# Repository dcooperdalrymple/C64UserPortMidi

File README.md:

# Commodore 64 User Port Midi Device
> Simple Midi Input & Output via the Commodore 64 User Port Interface<br />
> Created by D Cooper Dalrymple 2021 - [dcdalrymple.com](https://dcdalrymple.com/)<br />
> Licensed under GNU GPL V3.0<br />

I found myself in possession of a Commodore SX-64 and a desire to make music with it. After quickly finding [Cynthcart](https://www.qotile.net/cynthcart.html), I wasn't too happy about the idea of plugging both the Cynthcart cartridge and a separate Datel midi cartridge into in a [Mini X-Pander+](http://www.arkanixlabs.com/minixpander/) all sticking out of the hood of my SX-64. I had assumed that the User Port would have been a great interface for transmitting the necessary midi input data to whatever SID program you're jamming with. That's where this project comes in.

## Functionality
The concept is fairly simple: the stream of data from the midi input will be piped into a buffer by the microcontroller. After representing the value of each byte on the data bus of the user port (PB0-7), it will then trigger the user port's flag interrupt (FLAG2) to indicate new data is available. The compatible Commodore software that has an interrupt registered for the user port's flag pin then adds that 8-bit data register to a data buffer. The midi information would then need to be processed by the main loop of the software. Easy peasy!

I am aware that there are serial lines available on the user port that have been used for RS-232 communication and such, but I wanted to use the least amount of resources when transferring data from the bus to the Commodore software. A simple `lda $DD01` is all that is necessary to get the full byte during a flag interrupt.

The 8 bits of the user port are bi-directionally connected to the microcontroller, and a data transfer back to the microcontroller can be flagged using the dedicated GPIO pin, PC2. This functionality can be used to send midi data back out through the Midi Out port and perform additional functionality that has yet to be developed (channel filters, etc).

## Components
The microcontroller chosen for this project is the ATtiny2313. Using this micro reduces the total BOM by not requiring an external crystal oscillator, operating at 5V, including a hardware UART controller, and having just the right amount of GPIO.

Overall, the BOM is fairly minimal and using only through-hole components for easy assembly. To quickly get started making your own, I've assembled a [Digikey shared cart](https://www.digikey.com/short/7djhm4fz) with the exact hardware requirements and all of the necessary gerber files to order your own PCBs from a distributor such as PCBway.

## Development Status
I've just completed revision A of the hardware design which migrated from the ATtiny13 to ATtiny2313 and removed the need for a shift register. I've also added the components required MIDI output since the new microcontroller should be able to handle UART transmission with ease.

The firmware hasn't yet been updated for this new board design, but the functionality should mostly remain the same within the C64 software. I'll provide examples of bidirectional data transfer showcasing the output functionality of the new board once any bugs have been worked out.

I advise from producing your own units until the hardware and software have been fully developed.

## Software
A testing cartridge for the C64 is in development and mostly complete. This easily fits on a small 4kb/8kb lo-rom cart and could be compiled for floppy if needed. It can be run in emulation, but it isn't very useful unless the debugging data is enabled.

I plan to fork the Cynthcart repo once testing is completed to include full compatibility with this device.

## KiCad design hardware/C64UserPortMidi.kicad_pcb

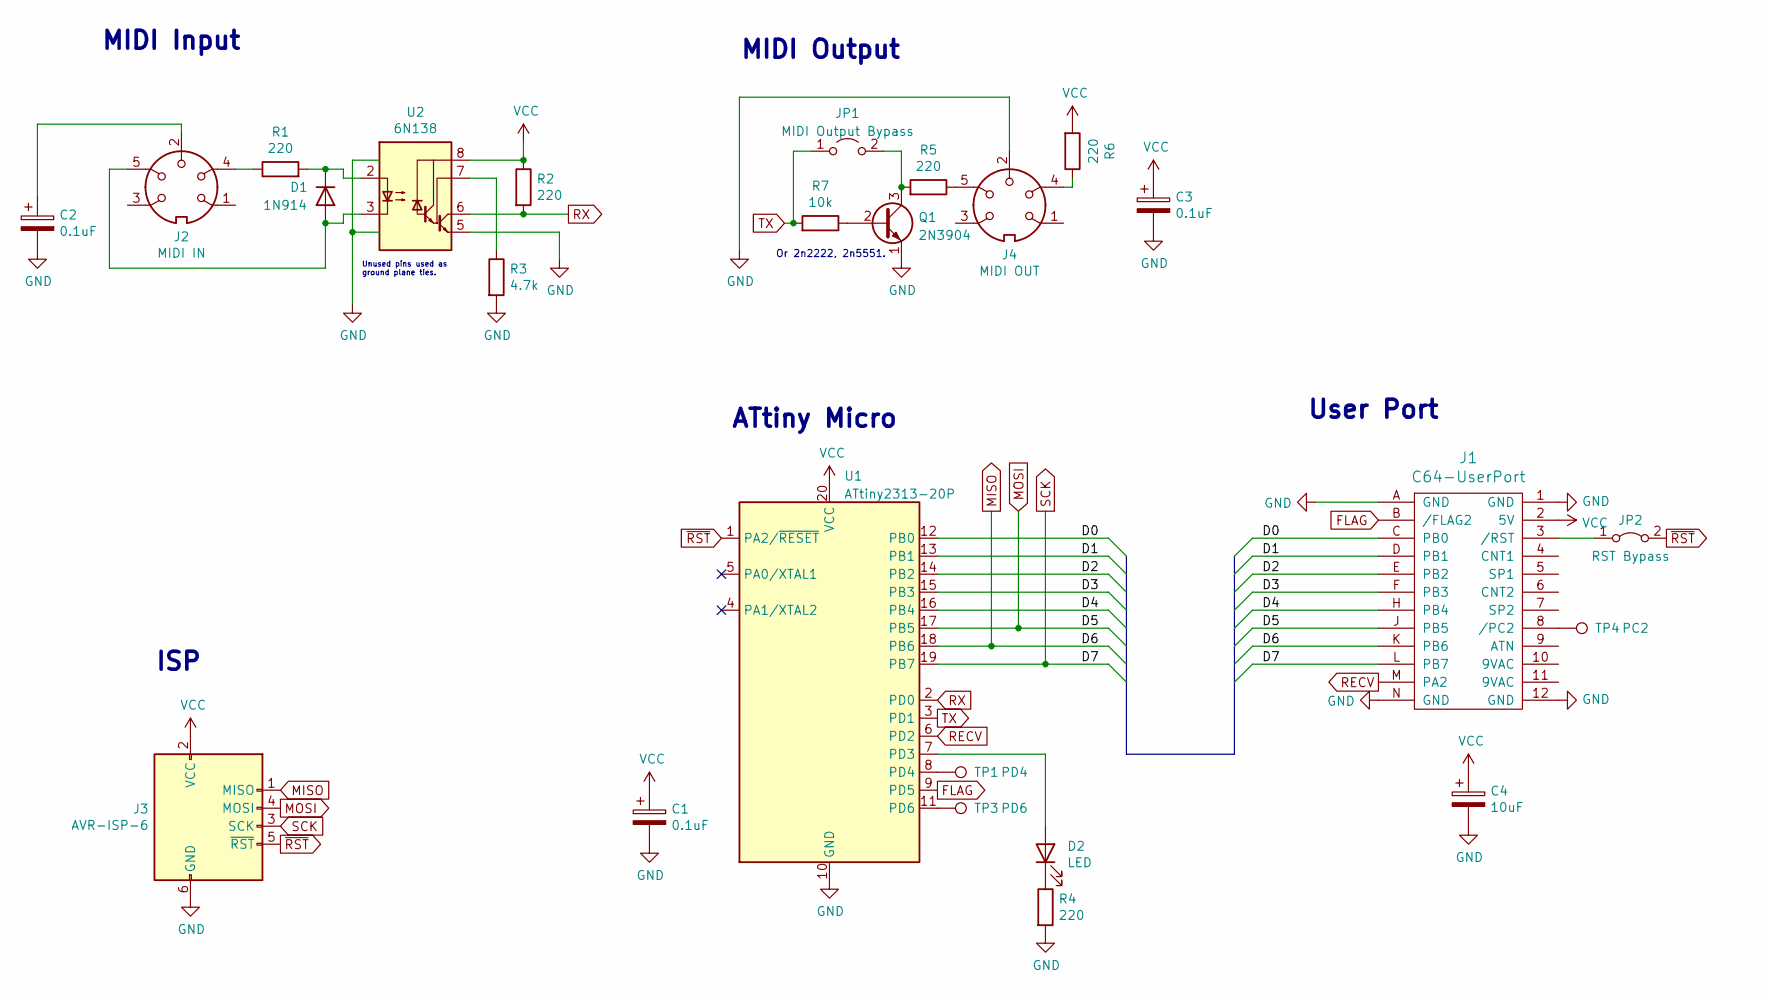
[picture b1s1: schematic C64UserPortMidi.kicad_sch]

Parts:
C1, C2, C3: 0.1uF; CP_Radial_D5.0mm_P2.00mm
C4: 10uF; CP_Radial_D5.0mm_P2.00mm
D1: 1N914; D_DO-35_SOD27_P7.62mm_Horizontal
D2: LED; LED_D3.0mm
J1: C64-UserPort; Connector_Edge_2x12_P3.96mm
J2: MIDI IN; din-5
J3: AVR-ISP-6; PinHeader_2x03_P2.54mm_Vertical
J4: MIDI OUT; din-5
JP1: MIDI Output Bypass; SolderJumper-2_P1.3mm_Open_RoundedPad1.0x1.5mm
JP2: RST Bypass; SolderJumper-2_P1.3mm_Bridged_RoundedPad1.0x1.5mm
Q1: 2N3904; TO-92_Inline
R1, R2, R4, R5, R6: 220; R_Axial_DIN0207_L6.3mm_D2.5mm_P7.62mm_Horizontal
R3: 4.7k; R_Axial_DIN0207_L6.3mm_D2.5mm_P7.62mm_Horizontal
R7: 10k; R_Axial_DIN0207_L6.3mm_D2.5mm_P7.62mm_Horizontal
TP1: PD4; TestPoint_THTPad_D1.5mm_Drill0.7mm
TP3: PD6; TestPoint_THTPad_D1.5mm_Drill0.7mm
TP4: PC2; TestPoint_THTPad_D1.5mm_Drill0.7mm
U1: ATtiny2313-20P; DIP-20_W7.62mm_Socket_LongPads
U2: 6N138; DIP-8_W7.62mm_Socket_LongPads

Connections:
/D0: J1.C (PB0), U1.12 (PB0)
/D1: J1.D (PB1), U1.13 (PB1)
/D2: J1.E (PB2), U1.14 (PB2)
/D3: J1.F (PB3), U1.15 (PB3)
/D4: J1.H (PB4), U1.16 (PB4)
FLAG: J1.B (/FLAG2), U1.9 (PD5)
GND: C1.2, C2.2, C3.2, C4.2, J1.1 (GND), J1.12 (GND), J1.A (GND), J1.N (GND), J3.6 (GND), J4.2, Q1.1 (E), R3.2, R4.2, U1.10 (GND), U2.1 (NC), U2.4 (NC), U2.5 (GND)
MISO: J1.K (PB6), J3.1 (MISO), U1.18 (PB6)
MOSI: J1.J (PB5), J3.4 (MOSI), U1.17 (PB5)
unnamed: C2.1, J2.2
unnamed: D1.1 (K), R1.2, U2.2 (C1)
unnamed: D1.2 (A), J2.5, U2.3 (C2)
unnamed: D2.1 (K), R4.1
unnamed: D2.2 (A), U1.7 (PD3)
unnamed: J1.3 (/RST), JP2.1 (A)
unnamed: J1.8 (/PC2), TP4.1
unnamed: J2.4, R1.1
unnamed: J4.4, R6.1
unnamed: J4.5, R5.1
unnamed: JP1.2 (B), Q1.3 (C), R5.2
unnamed: Q1.2 (B), R7.1
unnamed: R3.1, U2.7 (VO1)
unnamed: TP1.1, U1.8 (PD4)
unnamed: TP3.1, U1.11 (PD6)
RECV: J1.M (PA2), U1.6 (PD2)
RX: R2.2, U1.2 (PD0), U2.6 (VO2)
SCK: J1.L (PB7), J3.3 (SCK), U1.19 (PB7)
TX: JP1.1 (A), R7.2, U1.3 (PD1)
VCC: C1.1, C3.1, C4.1, J1.2 (5V), J3.2 (VCC), R2.1, R6.2, U1.20 (VCC), U2.8 (VCC)
~RST: J3.5 (~RST), JP2.2 (B), U1.1 (PA2/~RESET)

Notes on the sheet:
MIDI Input
MIDI Output
Or 2n2222, 2n5551.
User Port
ATtiny Micro
Unused pins used as ground plane ties.
ISP

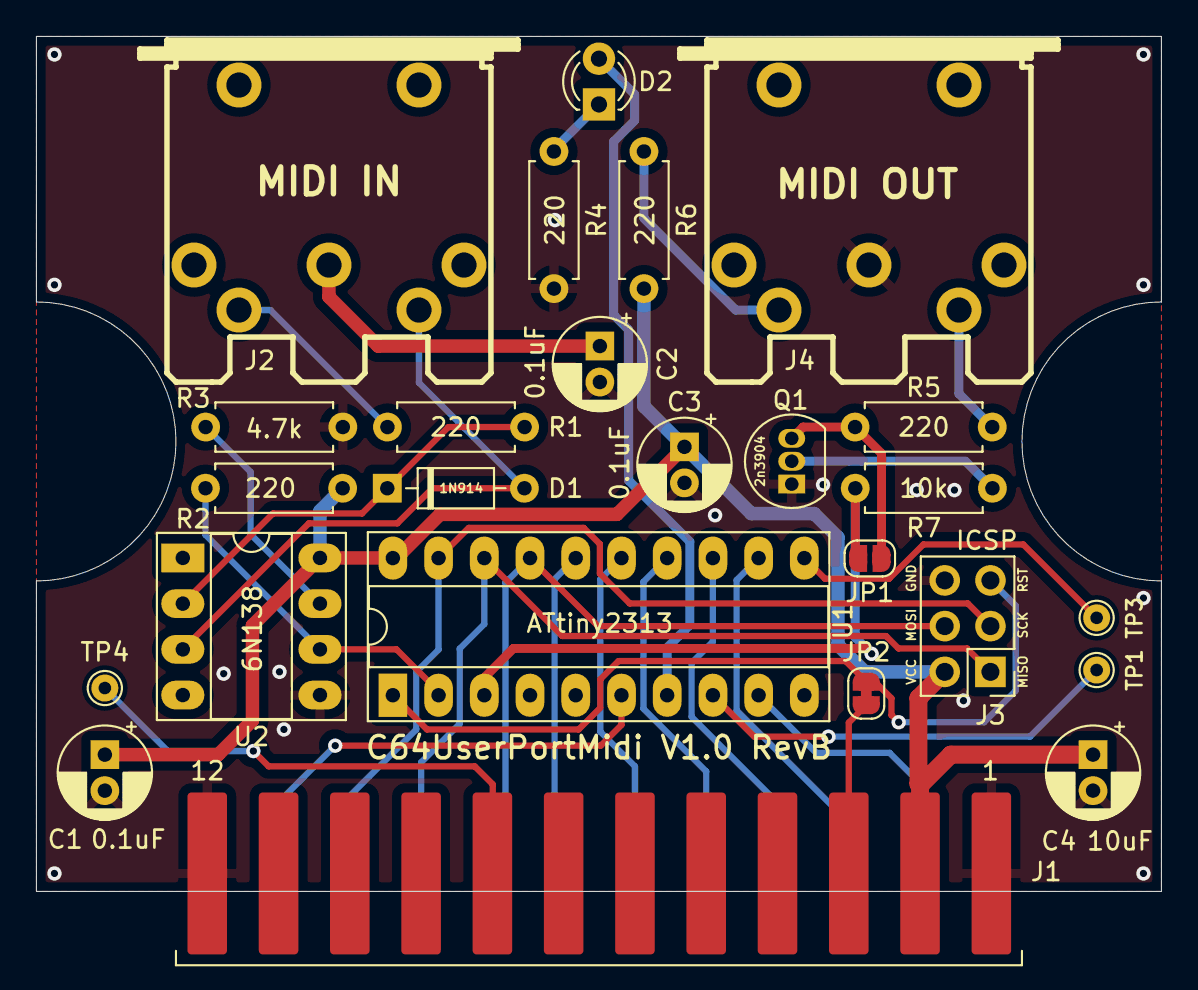
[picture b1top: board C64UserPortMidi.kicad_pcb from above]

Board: 2 copper layers, 62.5 x 47.5 mm, 25 parts (0 on the bottom side), 30 nets.

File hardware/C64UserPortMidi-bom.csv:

Reference, Value, Footprint, Datasheet
"C1","0.1uF","Capacitor_THT:CP_Radial_D5.0mm_P2.00mm",""
"C2","0.1uF","Capacitor_THT:CP_Radial_D5.0mm_P2.00mm",""
"C3","0.1uF","Capacitor_THT:CP_Radial_D5.0mm_P2.00mm",""
"C4","10uF","Capacitor_THT:CP_Radial_D5.0mm_P2.00mm",""
"D1","1N914","Diode_THT:D_DO-35_SOD27_P7.62mm_Horizontal","http://www.vishay.com/docs/85622/1n914.pdf"
"D2","LED","LED_THT:LED_D3.0mm",""
"J1","C64-UserPort","Commodore64C:Connector_Edge_2x12_P3.96mm",""
"J2","MIDI IN","Video Connectors:din-5","http://www.mouser.com/ds/2/18/40_c091_abd_e-75918.pdf"
"J3","AVR-ISP-6","Connector_PinHeader_2.54mm:PinHeader_2x03_P2.54mm_Vertical"," ~"
"J4","MIDI OUT","Video Connectors:din-5","http://www.mouser.com/ds/2/18/40_c091_abd_e-75918.pdf"
"JP1","MIDI Output Bypass","Jumper:SolderJumper-2_P1.3mm_Open_RoundedPad1.0x1.5mm",""
"JP2","RST Bypass","Jumper:SolderJumper-2_P1.3mm_Bridged_RoundedPad1.0x1.5mm",""
"Q1","2N3904","Package_TO_SOT_THT:TO-92_Inline","https://www.onsemi.com/pub/Collateral/2N3903-D.PDF"
"R1","220","Resistor_THT:R_Axial_DIN0207_L6.3mm_D2.5mm_P7.62mm_Horizontal",""
"R2","220","Resistor_THT:R_Axial_DIN0207_L6.3mm_D2.5mm_P7.62mm_Horizontal",""
"R3","4.7k","Resistor_THT:R_Axial_DIN0207_L6.3mm_D2.5mm_P7.62mm_Horizontal",""
"R4","220","Resistor_THT:R_Axial_DIN0207_L6.3mm_D2.5mm_P7.62mm_Horizontal",""
"R5","220","Resistor_THT:R_Axial_DIN0207_L6.3mm_D2.5mm_P7.62mm_Horizontal",""
"R6","220","Resistor_THT:R_Axial_DIN0207_L6.3mm_D2.5mm_P7.62mm_Horizontal",""
"R7","10k","Resistor_THT:R_Axial_DIN0207_L6.3mm_D2.5mm_P7.62mm_Horizontal",""
"TP1","PD4","TestPoint:TestPoint_THTPad_D1.5mm_Drill0.7mm",""
"TP3","PD6","TestPoint:TestPoint_THTPad_D1.5mm_Drill0.7mm",""
"TP4","PA2","TestPoint:TestPoint_THTPad_D1.5mm_Drill0.7mm",""
"U1","ATtiny2313-20P","Package_DIP:DIP-20_W7.62mm_Socket_LongPads","http://ww1.microchip.com/downloads/en/DeviceDoc/Atmel-2543-A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"
"U2","6N138","Package_DIP:DIP-8_W7.62mm_Socket_LongPads","http://www.onsemi.com/pub/Collateral/HCPL2731-D.pdf"

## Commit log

2021-02-25 Initial commit.
2021-02-25 Moved KiCad project to separate folder.
2021-02-25 C64 midi monitor software setup. Hello world example.
2021-03-02 First version of hardware pcb design completed.
2021-03-03 Updates to firmware. Separation of shift register functionality. New ATtiny13 tests.
2021-03-03 Added simple UART echo test.
2021-03-03 Successful tests of ATtiny13A hardware.
2021-03-03 ATtiny13 midi passthrough firmware complete. May need delay tweaking or midi-aware buffer.
2021-03-03 Added data led and latch filtering capacitor to hardware design.
2021-03-04 New readme, updated schematic assets, and BOM.
2021-03-09 Fixed pin number mixup from schematic symbol to pcb footprint on midi connector.
2021-03-10 Inverted flag output. Actually triggered on high, not low.
2021-03-10 Changed monitor makefile to output .bin instead of .prg.
2021-03-10 First rendition of C64 Midi Monitor. Mostly operational. Only showing hex data currently. I plan to add more parsing options with f-keys.
2021-03-10 Added hex and midi modes to monitor program.
2021-03-24 New flag test and MCU internal clock pushed up to 9.6Mhz.
2021-03-24 Updated firmware with packet-intelligent mode and user port flag improvements. Still unstable.
2021-03-24 C64 monitor software interrupt improvements and debug data.
2021-03-24 3d-printable case for user port dongle.
2021-03-24 Simple ATtiny13 interrupt test.
2021-03-25 Conversion of firmware and tests to AVR assembly. Still needs testing.
2021-03-25 Moved C64 definitions to separate header.
2021-03-25 Photos of first development unit and updated readme.
2021-04-05 Alterations to hardware to allow better handshaking between c64 and attiny. Flag code removed in favor of combined latch. Improved delay routines. Swapped flag test to transfer test for maximum speed.
2021-04-27 Improvements to MIDI test. Still needs work on receive interrupt.
2022-12-08 Interrupt midi test.
2022-12-08 Removed ESP8266 kicad submodule.
2022-12-08 Updated hardware design files for KiCad 6.0.
2022-12-11 New hardware design update. Version 1.0 Revision A.
2022-12-13 Converted firmware and tests to target ATtiny2313 and new hardware revision.
2022-12-15 Rename latch to flag in schematic.
2022-12-15 Changed ISP device to USBtinyISP.
2022-12-15 Updated delay script for 1MHz mode. Not incredibly accurate, but functional.
2023-01-03 Removed midi buffer from uart processing.
2023-01-03 Midi test rewritten to remove buffer requirement.
2023-01-03 Added led indication to transfer test.
2023-01-03 Fixed PA2 error in schematic, rerouted traces, and regenerated gerber files.
